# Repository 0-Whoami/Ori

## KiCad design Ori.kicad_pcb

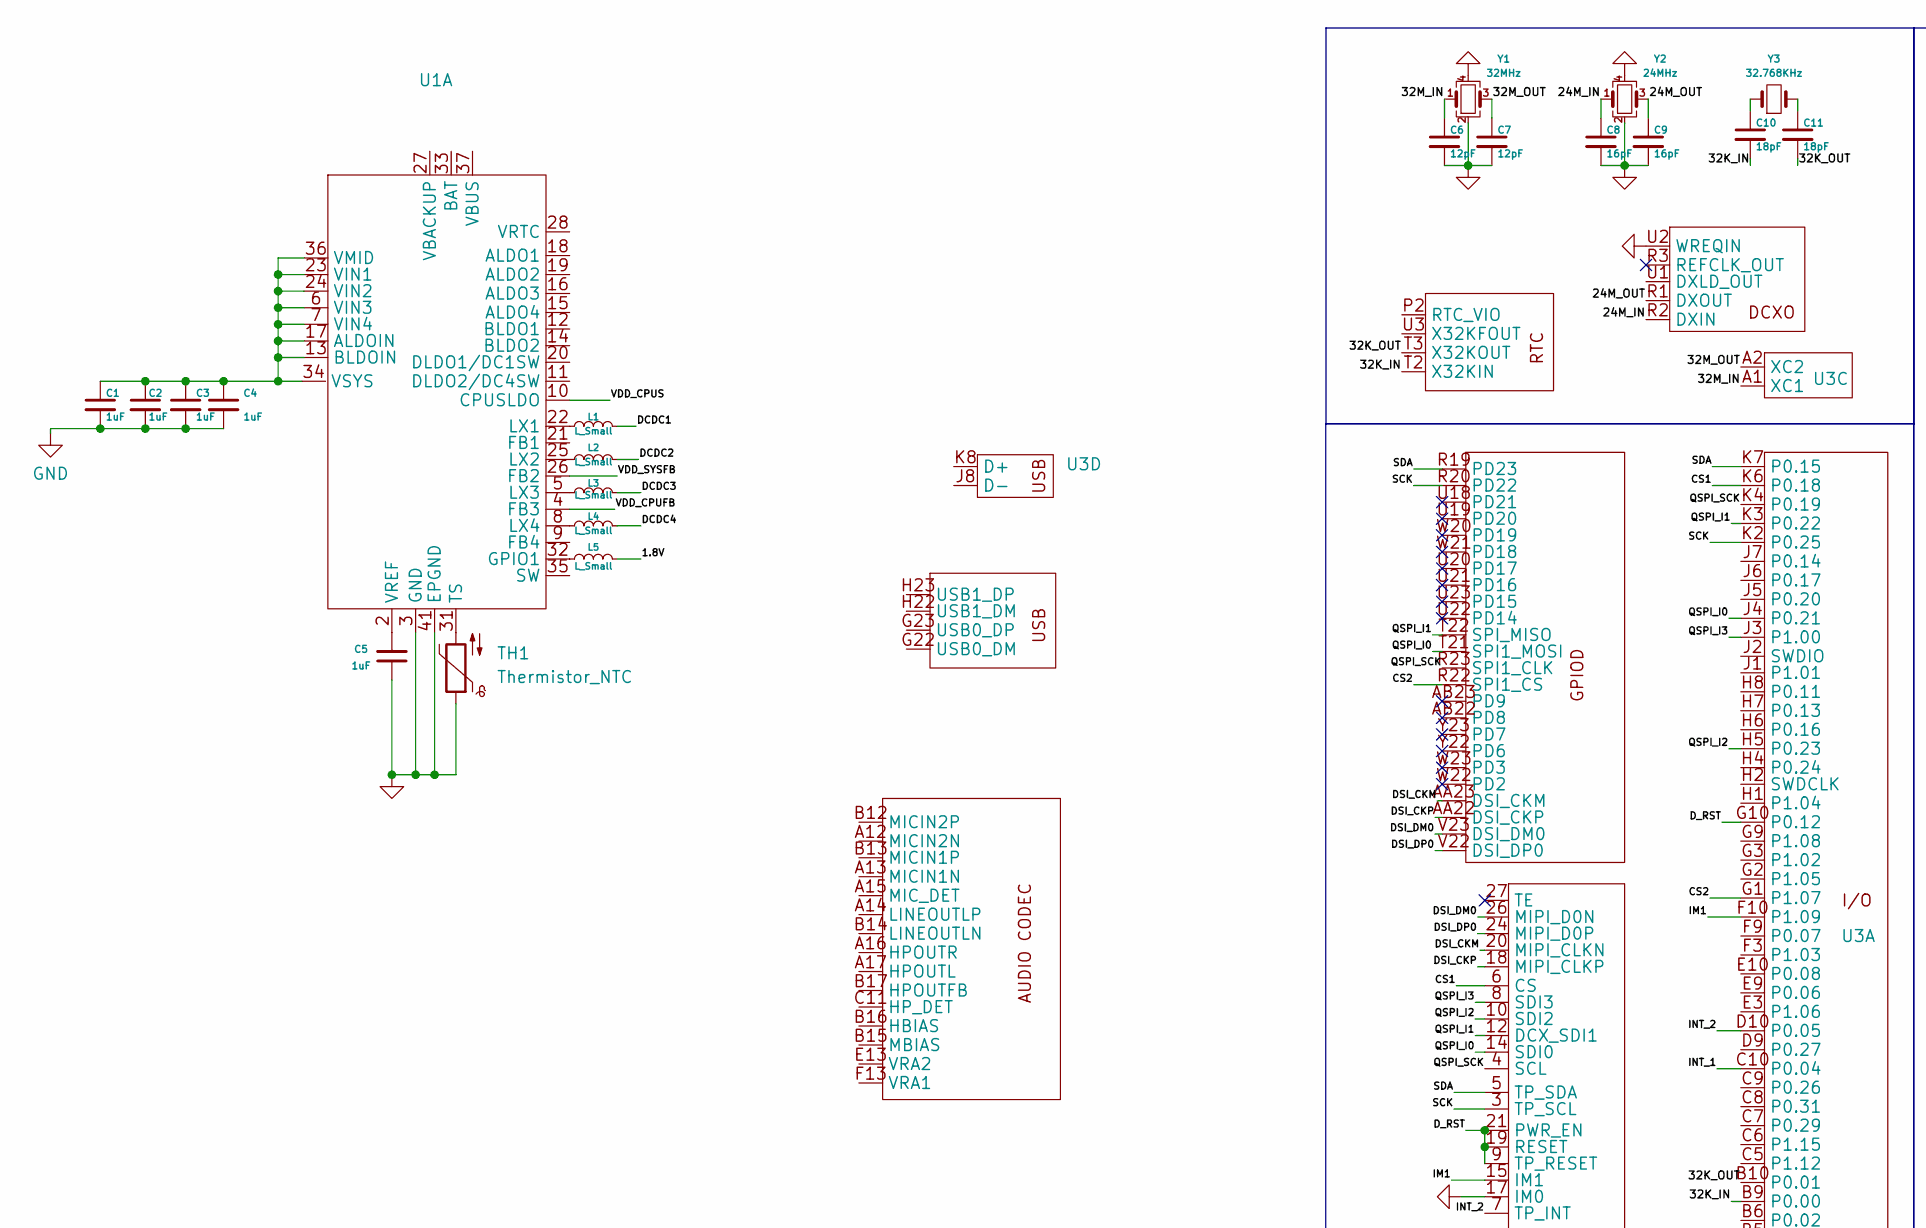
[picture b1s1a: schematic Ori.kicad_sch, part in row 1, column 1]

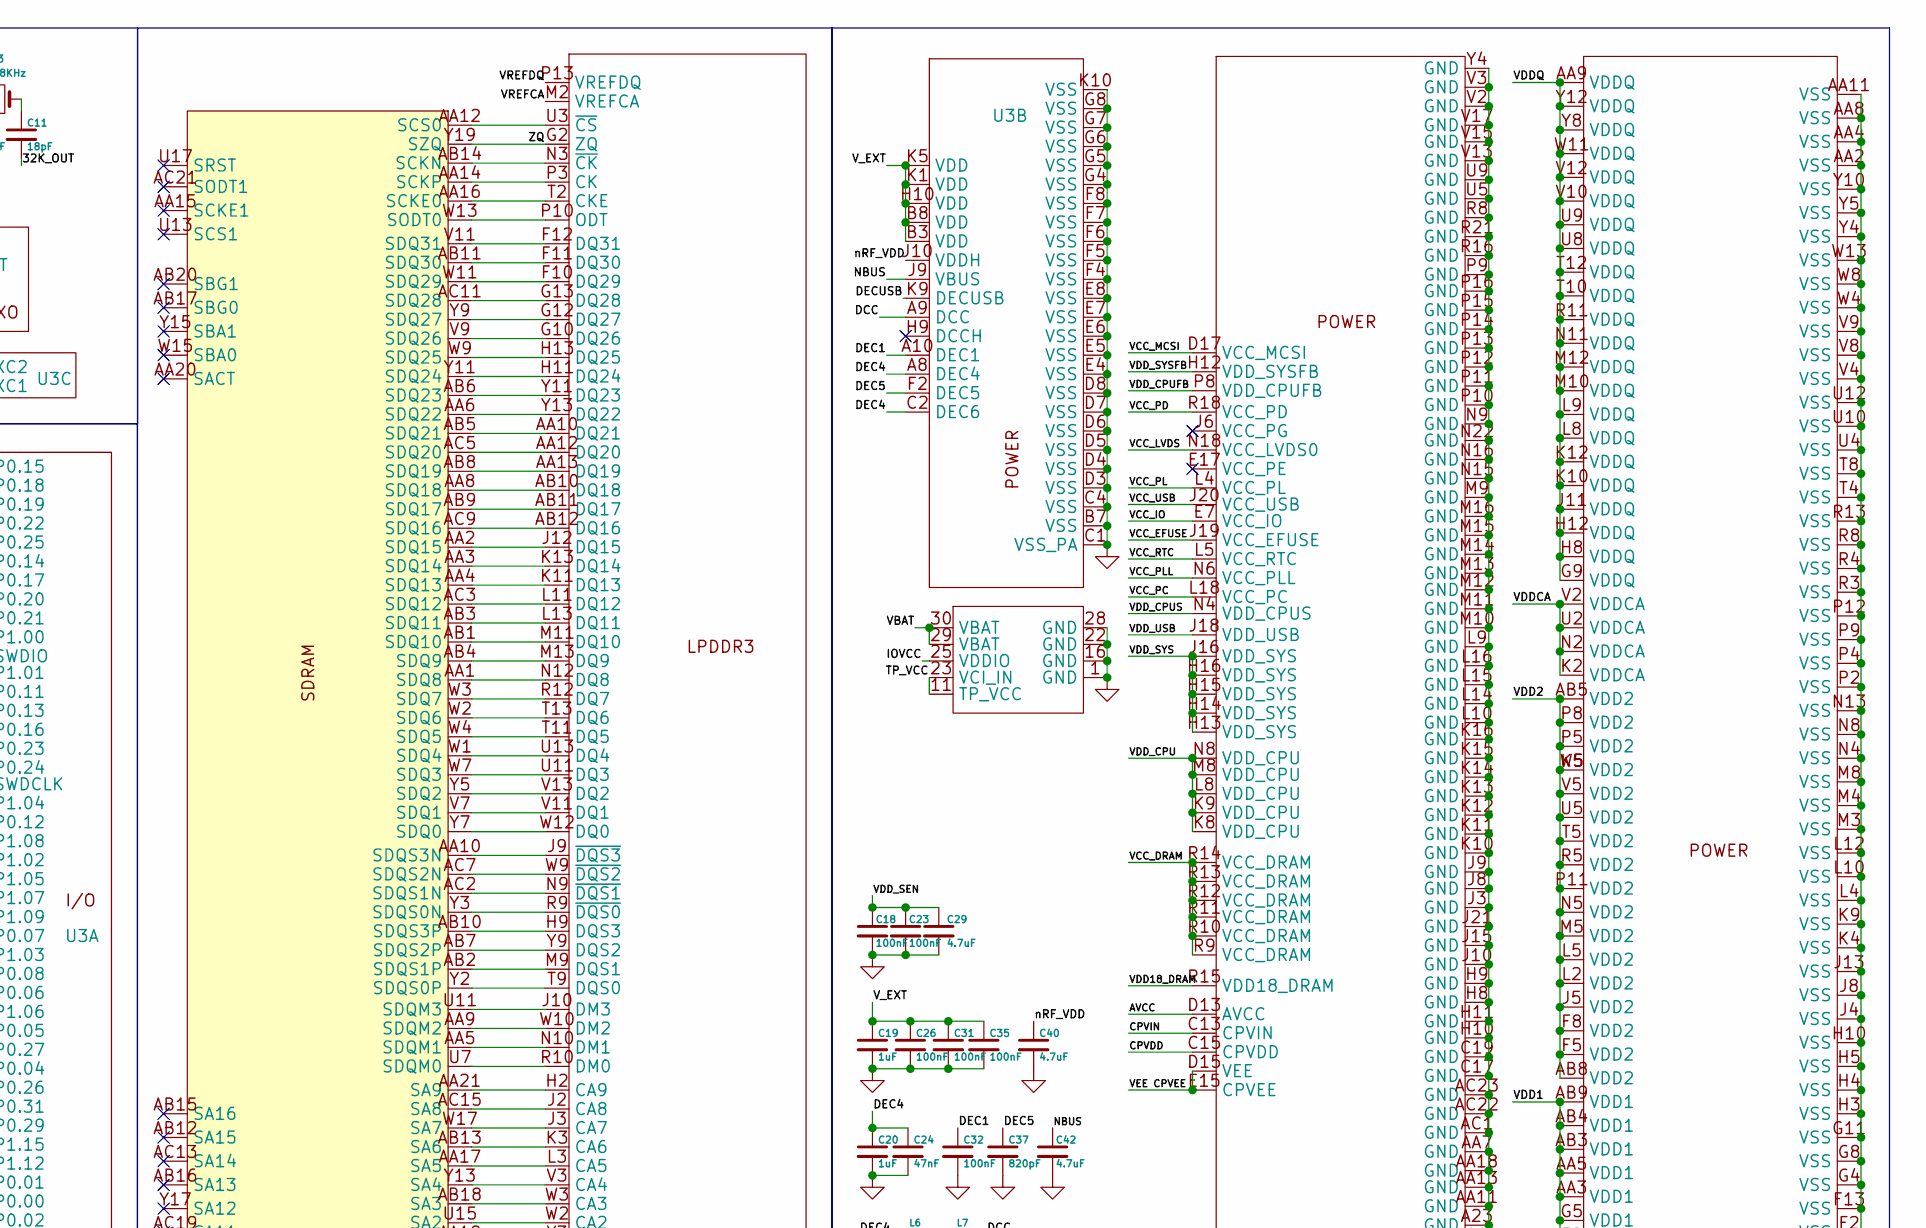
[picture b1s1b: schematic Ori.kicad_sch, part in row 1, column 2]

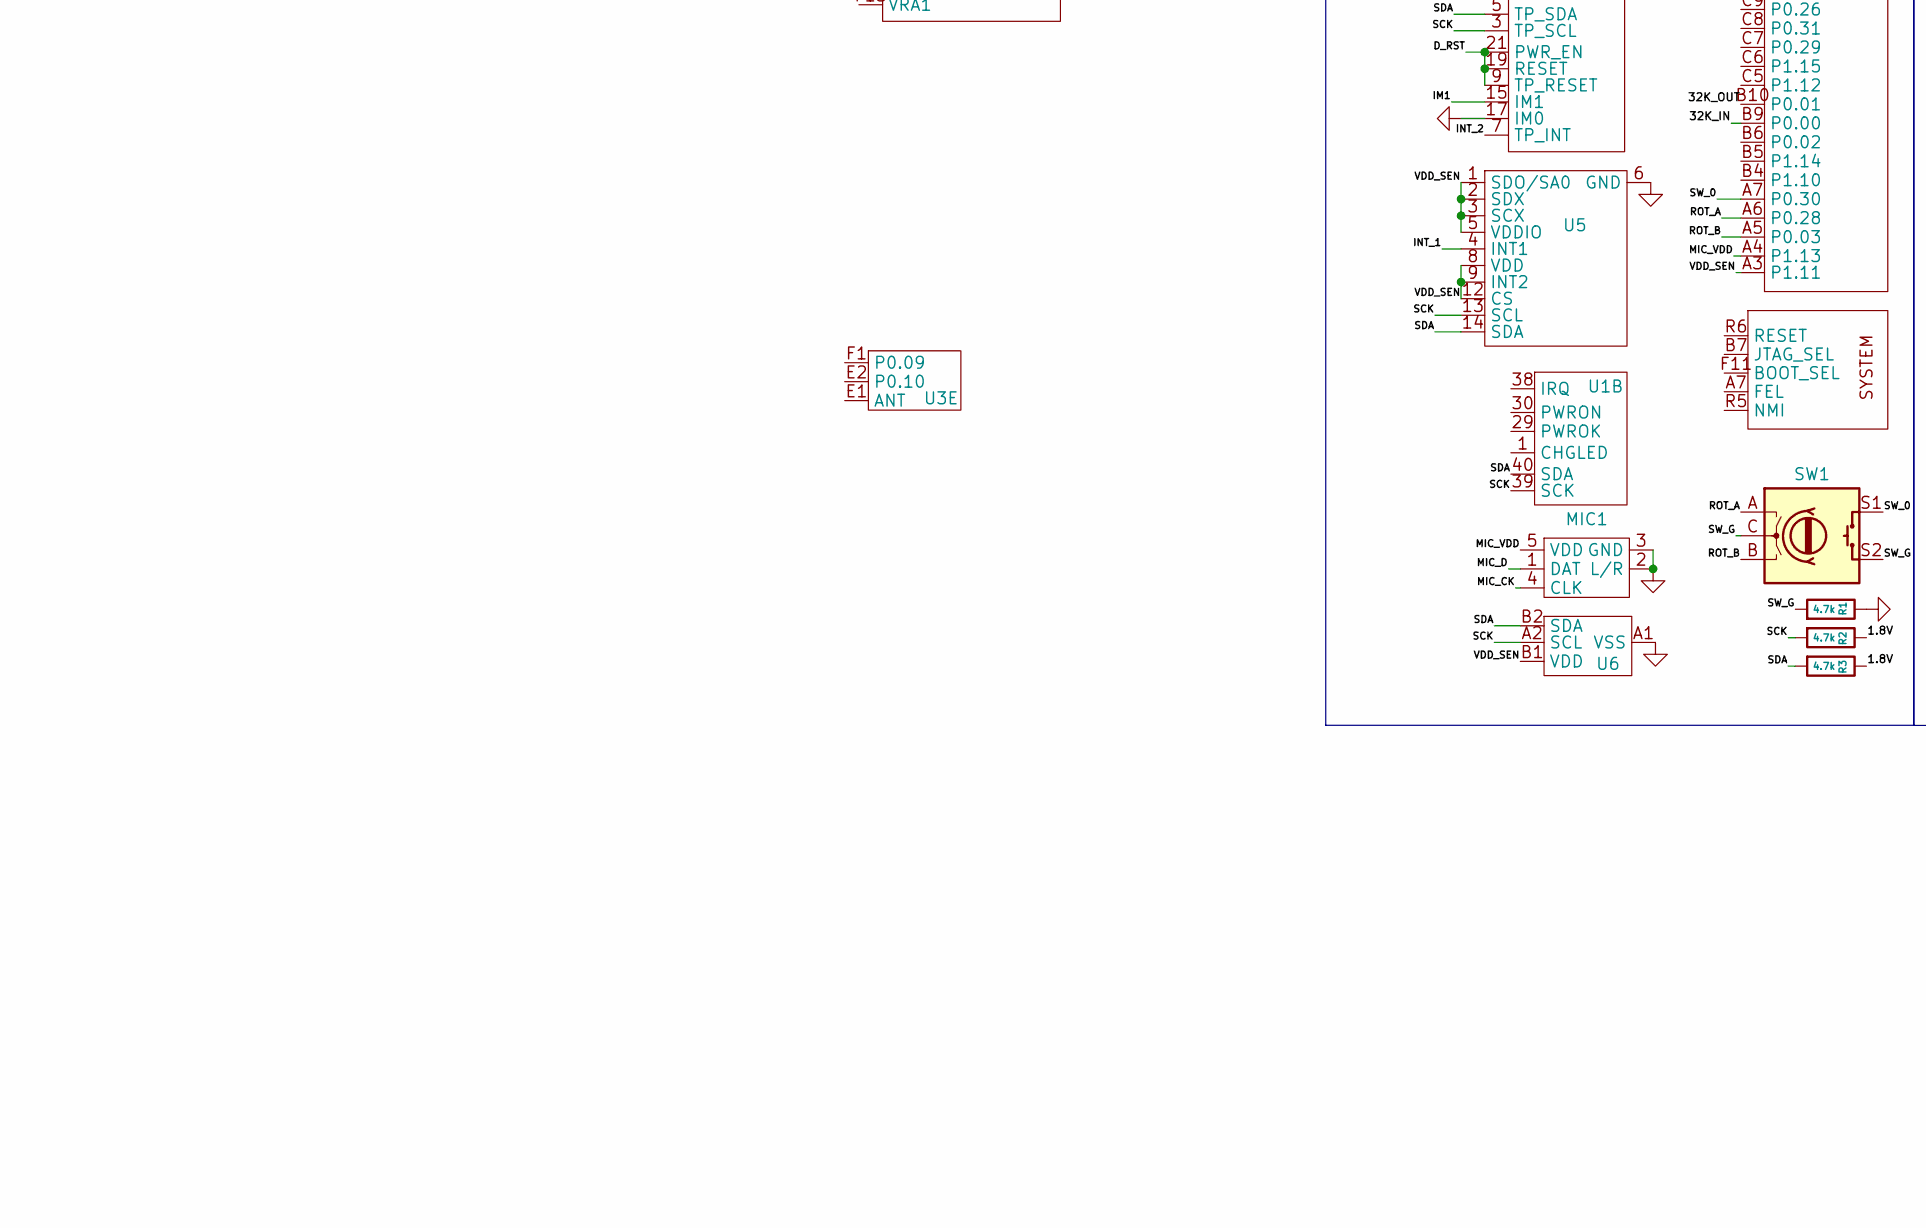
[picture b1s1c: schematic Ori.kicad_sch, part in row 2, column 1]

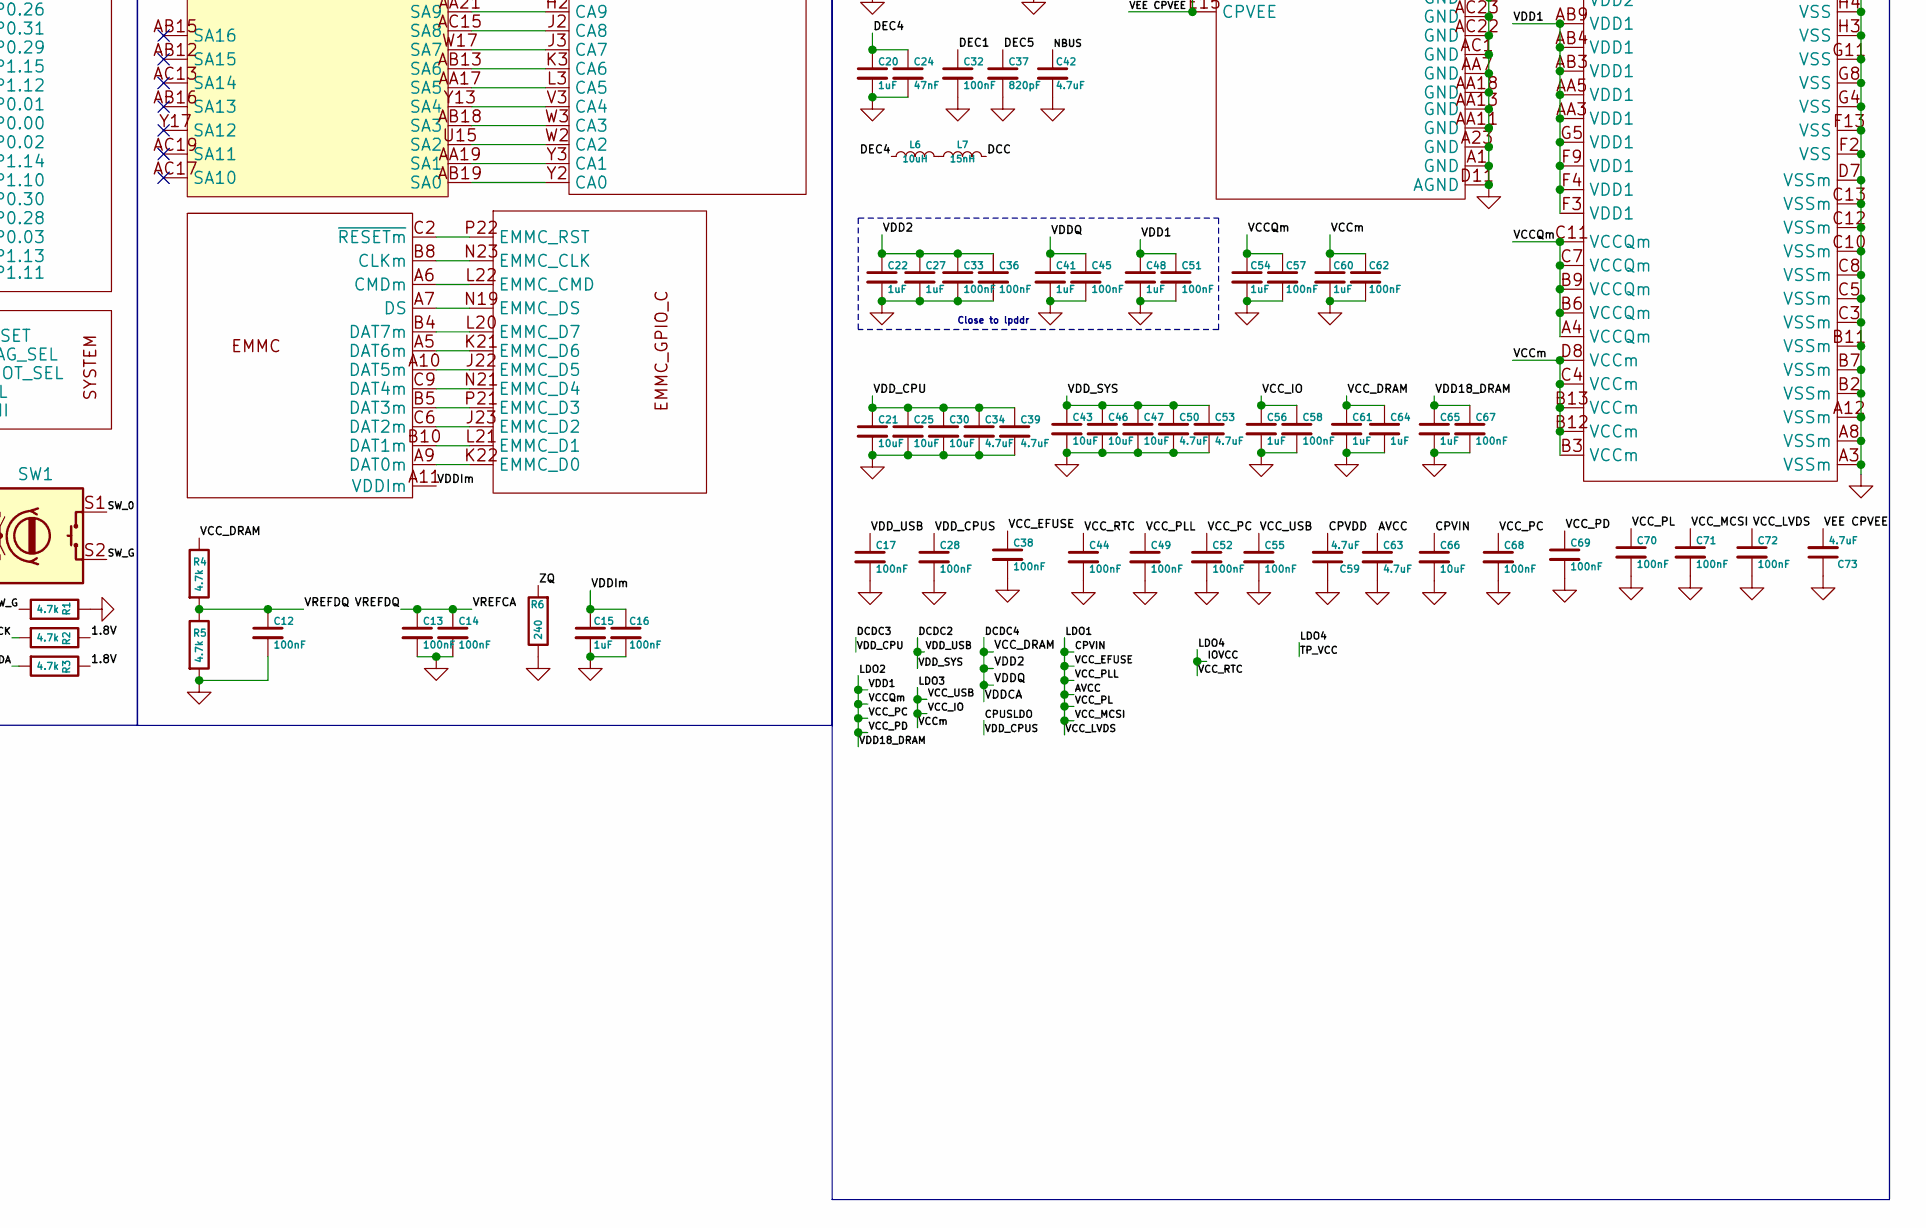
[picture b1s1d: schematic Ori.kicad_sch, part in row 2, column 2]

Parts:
C1, C2, C3, C4, C5, C15, C19, C20, C22, C27, C41, C48, C54, C56, C60, C61, C64, C65: 1uF; C_0402_1005Metric
C6, C7: 12pF; C_0402_1005Metric
C8, C9: 16pF; C_0402_1005Metric
C10, C11: 18pF; C_0402_1005Metric
C12, C13, C14, C16, C17, C18, C23, C26, C28, C31, C32, C33, C35, C36, C38, C44, C45, C49, C51, C52, C55, C57, C58, C62, C67, C68, C69, C70, C71, C72: 100nF; C_0402_1005Metric
C21, C25, C30, C43, C46, C47, C66: 10uF; C_0402_1005Metric
C24: 47nF; C_0402_1005Metric
C29, C34, C39, C40, C42, C50, C53, C59, C63, C73: 4.7uF; C_0402_1005Metric
C37: 820pF; C_0402_1005Metric
L1, L2, L3, L4, L5: L_Small; C_0402_1005Metric
L6: 10uH; C_0402_1005Metric
L7: 15nH; C_0402_1005Metric
MIC1: MMICT390200012
R1, R2, R3, R4, R5: 4.7k; C_0402_1005Metric
R6: 240; C_0402_1005Metric
SW1: RotaryEncoder_Switch
TH1: Thermistor_NTC; C_0402_1005Metric
U1: TQFN-40-1EP_5x5mm_P0.4mm_EP3.4x3.4mm
U2: LFBGA-346
U3: nRF52840_wlcsp
U4: (no value)
U5: LSM6DS3TR-C; LGA-14_3x2.5mm_P0.5mm_LayoutBorder3x4y
U6: 4 pin WLCPS
U7: FBGA-221
Y1: 32MHz
Y2: 24MHz
Y3: 32.768KHz

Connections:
/1.8V: L5.2, R2.1, R3.1
/24M_IN: C8.1, U2.R2 (DXIN), Y2.1
/24M_OUT: C9.1, U2.R1 (DXOUT), Y2.3
/32K_IN: C10.2, U2.T2 (X32KIN), U3.B9 (P0.00)
/32K_OUT: C11.2, U2.T3 (X32KOUT), U3.B10 (P0.01)
/32M_IN: C6.1, U3.A1 (XC1), Y1.1
/32M_OUT: C7.1, U3.A2 (XC2), Y1.3
/AVCC: C38.1, C49.1, C63.1, C66.1, C70.1, C71.1, C72.1, U2.C13 (CPVIN), U2.D13 (AVCC), U2.D17 (VCC_MCSI), U2.J19 (VCC_EFUSE), U2.L4 (VCC_PL), U2.N6 (VCC_PLL), U2.N18 (VCC_LVDS0)
/CPUSLDO: C28.1, U1.10 (CPUSLDO), U2.N4 (VDD_CPUS)
/CPVDD: C59.2, U2.C15 (CPVDD)
/CS1: U3.K6 (P0.18), U4.6 (CS)
/CS2: U2.R22 (SPI1_CS), U3.G1 (P1.07)
/DCC: L7.2, U3.A9 (DCC)
/DCDC1: L1.2
/DCDC2: C17.1, C43.1, C46.1, C47.1, C50.1, C53.1, L2.2, U2.H13 (VDD_SYS), U2.H14 (VDD_SYS), U2.H15 (VDD_SYS), U2.H16 (VDD_SYS), U2.J16 (VDD_SYS), U2.J18 (VDD_USB)
/DCDC3: C21.1, C25.1, C30.1, C34.1, C39.1, L3.2, U2.K8 (VDD_CPU), U2.K9 (VDD_CPU), U2.L8 (VDD_CPU), U2.M8 (VDD_CPU), U2.N8 (VDD_CPU)
/DCDC4: C22.1, C27.1, C33.1, C36.1, C41.1, C45.1, C61.1, C64.1, L4.2, R4.1, U2.R9 (VCC_DRAM), U2.R10 (VCC_DRAM), U2.R11 (VCC_DRAM), U2.R12 (VCC_DRAM), U2.R13 (VCC_DRAM), U2.R14 (VCC_DRAM), U7.AA9 (VDDQ), U7.AB5 (VDD2), U7.AB8 (VDD2), U7.F5 (VDD2), U7.F8 (VDD2), U7.G9 (VDDQ), U7.H8 (VDDQ), U7.H12 (VDDQ), U7.J5 (VDD2), U7.J11 (VDDQ), U7.K2 (VDDCA), U7.K5 (VDD2), U7.K10 (VDDQ), U7.K12 (VDDQ), U7.L2 (VDD2), U7.L5 (VDD2), U7.L8 (VDDQ), U7.L9 (VDDQ), U7.M5 (VDD2), U7.M10 (VDDQ), U7.M12 (VDDQ), U7.N2 (VDDCA), U7.N5 (VDD2), U7.N11 (VDDQ), U7.P5 (VDD2), U7.P8 (VDD2), U7.P11 (VDD2), U7.R5 (VDD2), U7.R11 (VDDQ), U7.T5 (VDD2), U7.T10 (VDDQ), U7.T12 (VDDQ), U7.U2 (VDDCA), U7.U5 (VDD2), U7.U8 (VDDQ), U7.U9 (VDDQ), U7.V2 (VDDCA), U7.V5 (VDD2), U7.V10 (VDDQ), U7.V12 (VDDQ), U7.W5 (VDD2), U7.W11 (VDDQ), U7.Y8 (VDDQ), U7.Y12 (VDDQ)
/DEC1: C32.1, U3.A10 (DEC1)
/DEC4: C20.1, C24.1, L6.1, U3.A8 (DEC4), U3.C2 (DEC6)
/DEC5: C37.1, U3.F2 (DEC5)
/DECUSB: U3.K9 (DECUSB)
/DSI_CKM: U2.AA23 (DSI_CKM), U4.20 (MIPI_CLKN)
/DSI_CKP: U2.AA22 (DSI_CKP), U4.18 (MIPI_CLKP)
/DSI_DM0: U2.V23 (DSI_DM0), U4.26 (MIPI_D0N)
/DSI_DP0: U2.V22 (DSI_DP0), U4.24 (MIPI_D0P)
/D_RST: U3.G10 (P0.12), U4.9 (TP_RESET), U4.19 (RESET), U4.21 (PWR_EN)
/IM1: U3.F10 (P1.09), U4.15 (IM1)
/INT_1: U3.C10 (P0.04), U5.4 (INT1)
/INT_2: U3.D10 (P0.05), U4.7 (TP_INT)
/IOVCC: C44.1, U2.L5 (VCC_RTC), U4.11 (TP_VCC), U4.23 (VCI_IN), U4.25 (VDDIO)
/LDO2: C48.1, C51.1, C52.1, C54.1, C57.1, C65.1, C67.1, C68.1, C69.1, U2.L18 (VCC_PC), U2.R15 (VDD18_DRAM), U2.R18 (VCC_PD), U7.A4 (VCCQm), U7.AA3 (VDD1), U7.AA5 (VDD1), U7.AB3 (VDD1), U7.AB4 (VDD1), U7.AB9 (VDD1), U7.B6 (VCCQm), U7.B9 (VCCQm), U7.C7 (VCCQm), U7.C11 (VCCQm), U7.F3 (VDD1), U7.F4 (VDD1), U7.F9 (VDD1), U7.G5 (VDD1)
/LDO3: C55.1, C56.1, C58.1, C60.1, C62.1, U2.E7 (VCC_IO), U2.J20 (VCC_USB), U7.B3 (VCCm), U7.B12 (VCCm), U7.B13 (VCCm), U7.C4 (VCCm), U7.D8 (VCCm)
/MIC_CK: MIC1.4 (CLK)
/MIC_D: MIC1.1 (DAT)
/MIC_VDD: MIC1.5 (VDD), U3.A4 (P1.13)
/NBUS: C42.1, U3.J9 (VBUS)
/QSPI_I0: U2.T21 (SPI1_MOSI), U3.J4 (P0.21), U4.14 (SDI0)
/QSPI_I1: U2.T22 (SPI_MISO), U3.K3 (P0.22), U4.12 (DCX_SDI1)
/QSPI_I2: U3.H5 (P0.23), U4.10 (SDI2)
/QSPI_I3: U3.J3 (P1.00), U4.8 (SDI3)
/QSPI_SCK: U2.R23 (SPI1_CLK), U3.K4 (P0.19), U4.4 (SCL)
/ROT_A: SW1.A, U3.A6 (P0.28)
/ROT_B: SW1.B, U3.A5 (P0.03)
/SCK: R2.2, U1.39 (SCK), U2.R20 (PD22), U3.K2 (P0.25), U4.3 (TP_SCL), U5.13 (SCL), U6.A2 (SCL)
/SDA: R3.2, U1.40 (SDA), U2.R19 (PD23), U3.K7 (P0.15), U4.5 (TP_SDA), U5.14 (SDA), U6.B2 (SDA)
/SW_0: SW1.S1, U3.A7 (P0.30)
/SW_G: R1.2, SW1.C, SW1.S2
/VDDIm: C15.1, C16.1, U7.A11 (VDDIm)
/VDD_CPUFB: U1.4 (FB3), U2.P8 (VDD_CPUFB)
/VDD_SEN: C18.1, C23.1, C29.1, U3.A3 (P1.11), U5.1 (SDO/SA0), U5.2 (SDX), U5.3 (SCX), U5.5 (VDDIO), U5.8 (VDD), U5.9 (INT2), U5.12 (CS), U6.B1 (VDD)
/VDD_SYSFB: U1.26 (FB2), U2.H12 (VDD_SYSFB)
/VEE CPVEE: C73.2, U2.D15 (VEE), U2.E15 (CPVEE)
/VREFCA: C12.1, C13.1, C14.1, R4.2, R5.1, U7.M2 (VREFCA), U7.P13 (VREFDQ)
/V_EXT: C19.1, C26.1, C31.1, C35.1, U3.B3 (VDD), U3.B8 (VDD), U3.H10 (VDD), U3.K1 (VDD), U3.K5 (VDD)
/ZQ: R6.2, U2.Y19 (SZQ), U7.G2 (ZQ)
/nRF_VDD: C40.1, U3.J10 (VDDH)
GND: C1.2, C2.2, C3.2, C4.2, C5.1, C6.2, C7.2, C8.2, C9.2, C12.2, C13.2, C14.2, C15.2, C16.2, C17.2, C18.2, C19.2, C20.2, C21.2, C22.2, C23.2, C24.2, C25.2, C26.2, C27.2, C28.2, C29.2, C30.2, C31.2, C32.2, C33.2, C34.2, C35.2, C36.2, C37.2, C38.2, C39.2, C40.2, C41.2, C42.2, C43.2, C44.2, C45.2, C46.2, C47.2, C48.2, C49.2, C50.2, C51.2, C52.2, C53.2, C54.2, C55.2, C56.2, C57.2, C58.2, C59.1, C60.2, C61.2, C62.2, C63.2, C64.2, C65.2, C66.2, C67.2, C68.2, C69.2, C70.2, C71.2, C72.2, C73.1, MIC1.2 (L/R), MIC1.3 (GND), R1.1, R5.2, R6.1, TH1.1, U1.3 (GND), U1.41 (EPGND), U2.A1 (GND), U2.A23 (GND), U2.AA7 (GND), U2.AA11 (GND), U2.AA13 (GND), U2.AA18 (GND), U2.AC1 (GND), U2.AC22 (GND), U2.AC23 (GND), U2.C17 (GND), U2.C19 (GND), U2.D11 (AGND), U2.H8 (GND), U2.H9 (GND), U2.H10 (GND), U2.H11 (GND), U2.J3 (GND), U2.J8 (GND), U2.J9 (GND), U2.J10 (GND), U2.J15 (GND), U2.J21 (GND), U2.K10 (GND), U2.K11 (GND), U2.K12 (GND), U2.K13 (GND), U2.K14 (GND), U2.K15 (GND), U2.K16 (GND), U2.L9 (GND), U2.L10 (GND), U2.L14 (GND), U2.L15 (GND), U2.L16 (GND), U2.M9 (GND), U2.M10 (GND), U2.M11 (GND), U2.M12 (GND), U2.M13 (GND), U2.M14 (GND), U2.M15 (GND), U2.M16 (GND), U2.N9 (GND), U2.N15 (GND), U2.N16 (GND), U2.N22 (GND), U2.P9 (GND), U2.P10 (GND), U2.P11 (GND), U2.P12 (GND), U2.P13 (GND), U2.P14 (GND), U2.P15 (GND), U2.P16 (GND), U2.R8 (GND), U2.R16 (GND), U2.R21 (GND), U2.U2 (WREQIN), U2.U5 (GND), U2.U9 (GND), U2.V2 (GND), U2.V3 (GND), U2.V13 (GND), U2.V15 (GND), U2.V17 (GND), U2.Y4 (GND), U3.B7 (VSS), U3.C1 (VSS_PA), U3.C4 (VSS), U3.D3 (VSS), U3.D4 (VSS), U3.D5 (VSS), U3.D6 (VSS), U3.D7 (VSS), U3.D8 (VSS), U3.E4 (VSS), U3.E5 (VSS), U3.E6 (VSS), U3.E7 (VSS), U3.E8 (VSS), U3.F4 (VSS), U3.F5 (VSS), U3.F6 (VSS), U3.F7 (VSS), U3.F8 (VSS), U3.G4 (VSS), U3.G5 (VSS), U3.G6 (VSS), U3.G7 (VSS), U3.G8 (VSS), U3.K10 (VSS), U4.1 (GND), U4.16 (GND), U4.17 (IM0), U4.22 (GND), U4.28 (GND), U5.6 (GND), U6.A1 (VSS), U7.A3 (VSSm), U7.A8 (VSSm), U7.A12 (VSSm), U7.AA2 (VSS), U7.AA4 (VSS), U7.AA8 (VSS), U7.AA11 (VSS), U7.B2 (VSSm), U7.B7 (VSSm), U7.B11 (VSSm), U7.C3 (VSSm), U7.C5 (VSSm), U7.C8 (VSSm), U7.C10 (VSSm), U7.C12 (VSSm), U7.C13 (VSSm), U7.D7 (VSSm), U7.F2 (VSS), U7.F13 (VSS), U7.G4 (VSS), U7.G8 (VSS), U7.G11 (VSS), U7.H3 (VSS), U7.H4 (VSS), U7.H5 (VSS), U7.H10 (VSS), U7.J4 (VSS), U7.J8 (VSS), U7.J13 (VSS), U7.K4 (VSS), U7.K9 (VSS), U7.L4 (VSS), U7.L10 (VSS), U7.L12 (VSS), U7.M3 (VSS), U7.M4 (VSS), U7.M8 (VSS), U7.N4 (VSS), U7.N8 (VSS), U7.N13 (VSS), U7.P2 (VSS), U7.P4 (VSS), U7.P9 (VSS), U7.P12 (VSS), U7.R3 (VSS), U7.R4 (VSS), U7.R8 (VSS), U7.R13 (VSS), U7.T4 (VSS), U7.T8 (VSS), U7.U4 (VSS), U7.U10 (VSS), U7.U12 (VSS), U7.V4 (VSS), U7.V8 (VSS), U7.V9 (VSS), U7.W4 (VSS), U7.W8 (VSS), U7.W13 (VSS), U7.Y4 (VSS), U7.Y5 (VSS), U7.Y10 (VSS), Y1.2, Y1.4, Y2.2, Y2.4
unnamed: C10.1, Y3.1
unnamed: C11.1, Y3.2
unnamed: L6.2, L7.1
unnamed: C1.1, C2.1, C3.1, C4.1, U1.6 (VIN3), U1.7 (VIN4), U1.13 (BLDOIN), U1.17 (ALDOIN), U1.23 (VIN1), U1.24 (VIN2), U1.34 (VSYS), U1.36 (VMID)
unnamed: L5.1, U1.32 (GPIO1)
unnamed: L1.1, U1.22 (LX1)
unnamed: L2.1, U1.25 (LX2)
unnamed: L3.1, U1.5 (LX3)
unnamed: L4.1, U1.8 (LX4)
unnamed: TH1.2, U1.31 (TS)
unnamed: C5.2, U1.2 (VREF)
unnamed: U2.AB19 (SA0), U7.Y2 (CA0)
unnamed: U2.AA19 (SA1), U7.Y3 (CA1)
unnamed: U2.U15 (SA2), U7.W2 (CA2)
unnamed: U2.AB18 (SA3), U7.W3 (CA3)
unnamed: U2.Y13 (SA4), U7.V3 (CA4)
unnamed: U2.AA17 (SA5), U7.L3 (CA5)
unnamed: U2.AB13 (SA6), U7.K3 (CA6)
unnamed: U2.W17 (SA7), U7.J3 (CA7)
unnamed: U2.AC15 (SA8), U7.J2 (CA8)
unnamed: U2.AA21 (SA9), U7.H2 (CA9)
unnamed: U2.AA16 (SCKE0), U7.T2 (CKE)
unnamed: U2.AB14 (SCKN), U7.N3 (~CK)
unnamed: U2.AA14 (SCKP), U7.P3 (CK)
unnamed: U2.AA12 (SCS0), U7.U3 (~CS)
unnamed: U2.Y7 (SDQ0), U7.W12 (DQ0)
unnamed: U2.V7 (SDQ1), U7.V11 (DQ1)
unnamed: U2.Y5 (SDQ2), U7.V13 (DQ2)
unnamed: U2.W7 (SDQ3), U7.U11 (DQ3)
unnamed: U2.W1 (SDQ4), U7.U13 (DQ4)
unnamed: U2.W4 (SDQ5), U7.T11 (DQ5)
unnamed: U2.W2 (SDQ6), U7.T13 (DQ6)
unnamed: U2.W3 (SDQ7), U7.R12 (DQ7)
unnamed: U2.AA1 (SDQ8), U7.N12 (DQ8)
unnamed: U2.AB4 (SDQ9), U7.M13 (DQ9)
unnamed: U2.AB1 (SDQ10), U7.M11 (DQ10)
unnamed: U2.AB3 (SDQ11), U7.L13 (DQ11)
unnamed: U2.AC3 (SDQ12), U7.L11 (DQ12)
unnamed: U2.AA4 (SDQ13), U7.K11 (DQ13)
unnamed: U2.AA3 (SDQ14), U7.K13 (DQ14)
unnamed: U2.AA2 (SDQ15), U7.J12 (DQ15)
unnamed: U2.AC9 (SDQ16), U7.AB12 (DQ16)
unnamed: U2.AB9 (SDQ17), U7.AB11 (DQ17)
unnamed: U2.AA8 (SDQ18), U7.AB10 (DQ18)
unnamed: U2.AB8 (SDQ19), U7.AA13 (DQ19)
unnamed: U2.AC5 (SDQ20), U7.AA12 (DQ20)
unnamed: U2.AB5 (SDQ21), U7.AA10 (DQ21)
unnamed: U2.AA6 (SDQ22), U7.Y13 (DQ22)
unnamed: U2.AB6 (SDQ23), U7.Y11 (DQ23)
unnamed: U2.Y11 (SDQ24), U7.H11 (DQ24)
unnamed: U2.W9 (SDQ25), U7.H13 (DQ25)
unnamed: U2.V9 (SDQ26), U7.G10 (DQ26)
unnamed: U2.Y9 (SDQ27), U7.G12 (DQ27)
unnamed: U2.AC11 (SDQ28), U7.G13 (DQ28)
unnamed: U2.W11 (SDQ29), U7.F10 (DQ29)
unnamed: U2.AB11 (SDQ30), U7.F11 (DQ30)
unnamed: U2.V11 (SDQ31), U7.F12 (DQ31)
unnamed: U2.U7 (SDQM0), U7.R10 (DM0)
unnamed: U2.AA5 (SDQM1), U7.N10 (DM1)
unnamed: U2.AA9 (SDQM2), U7.W10 (DM2)
unnamed: U2.U11 (SDQM3), U7.J10 (DM3)
unnamed: U2.Y3 (SDQS0N), U7.R9 (~DQS0)
unnamed: U2.Y2 (SDQS0P), U7.T9 (DQS0)
unnamed: U2.AC2 (SDQS1N), U7.N9 (~DQS1)
unnamed: U2.AB2 (SDQS1P), U7.M9 (DQS1)
unnamed: U2.AC7 (SDQS2N), U7.W9 (~DQS2)
unnamed: U2.AB7 (SDQS2P), U7.Y9 (DQS2)
unnamed: U2.AA10 (SDQS3N), U7.J9 (~DQS3)
unnamed: U2.AB10 (SDQS3P), U7.H9 (DQS3)
unnamed: U2.W13 (SODT0), U7.P10 (ODT)
unnamed: U2.N23 (EMMC_CLK), U7.B8 (CLKm)
unnamed: U2.L22 (EMMC_CMD), U7.A6 (CMDm)
unnamed: U2.K22 (EMMC_D0), U7.A9 (DAT0m)
unnamed: U2.L21 (EMMC_D1), U7.B10 (DAT1m)
unnamed: U2.J23 (EMMC_D2), U7.C6 (DAT2m)
unnamed: U2.P21 (EMMC_D3), U7.B5 (DAT3m)
unnamed: U2.N21 (EMMC_D4), U7.C9 (DAT4m)
unnamed: U2.J22 (EMMC_D5), U7.A10 (DAT5m)
unnamed: U2.K21 (EMMC_D6), U7.A5 (DAT6m)
unnamed: U2.L20 (EMMC_D7), U7.B4 (DAT7m)
unnamed: U2.N19 (EMMC_DS), U7.A7 (DS)
unnamed: U2.P22 (EMMC_RST), U7.C2 (~RESETm)
unnamed: U4.29 (VBAT), U4.30 (VBAT)

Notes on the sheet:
Close to lpddr

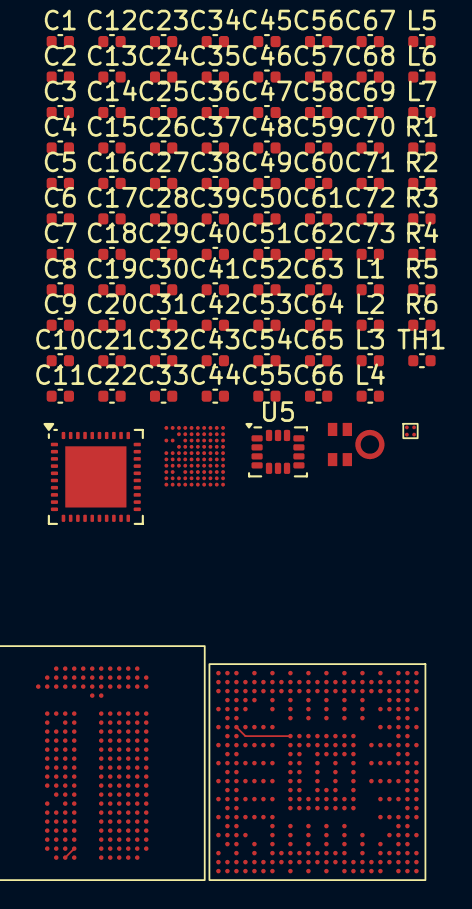
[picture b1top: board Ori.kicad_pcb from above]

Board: 4 copper layers, 94 parts (0 on the bottom side), 119 nets.

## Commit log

2025-06-12 test
2025-07-20 test2
